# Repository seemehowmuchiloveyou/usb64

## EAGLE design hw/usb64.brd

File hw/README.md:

# Breakout PCB
* This board was designed using [Autodesk Eagle](https://www.autodesk.com/products/eagle/overview). You can edit the `.brd` and `.sch` with this program.
* You can order via KitSpace: https://kitspace.org/boards/github.com/ryzee119/usb64/.

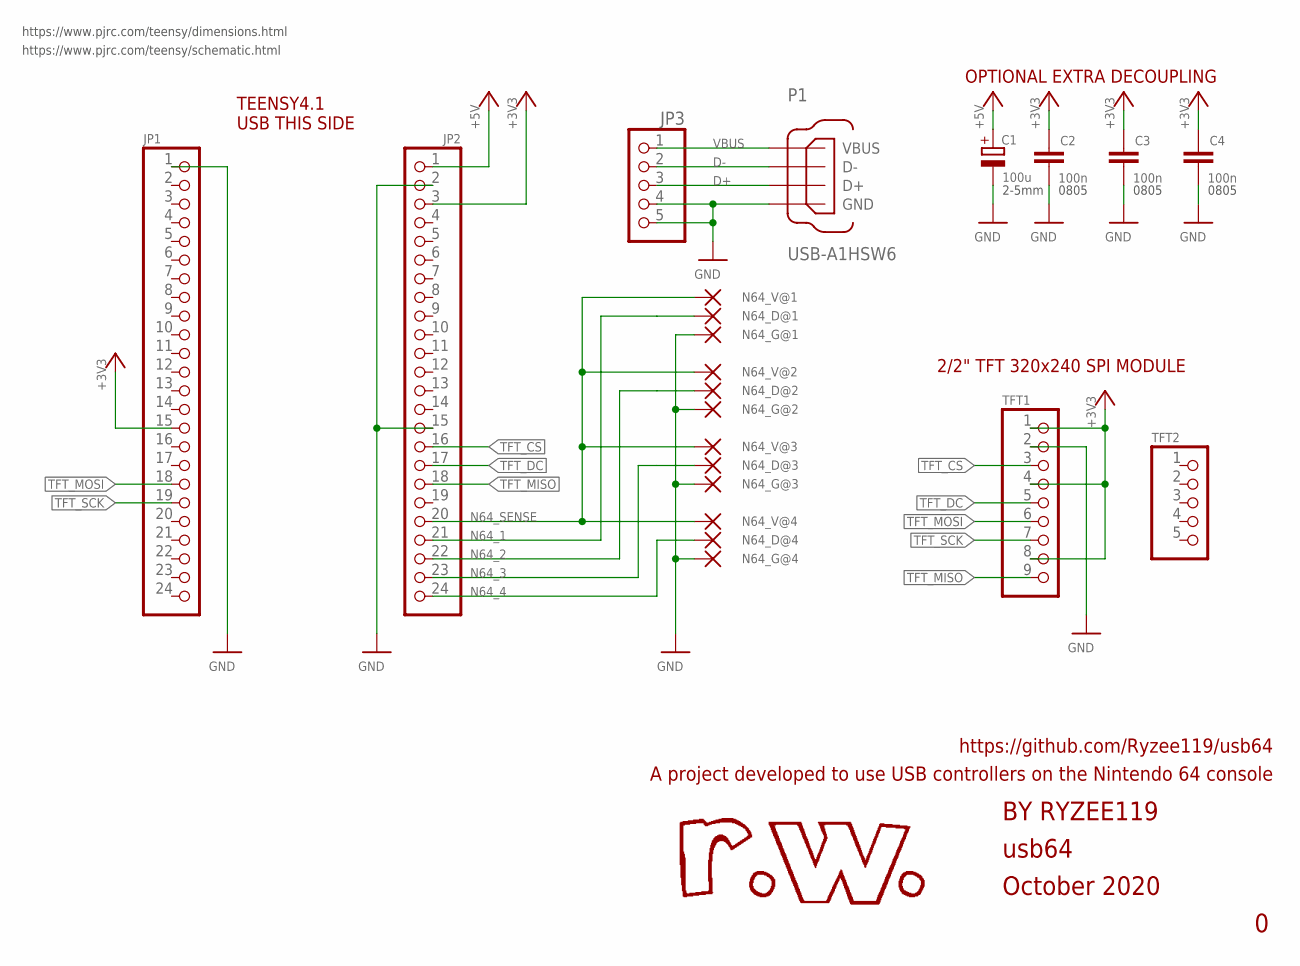
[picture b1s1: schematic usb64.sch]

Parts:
C1: 100u; E2-5
C2, C3, C4: 100n; C0805K
JP1, JP2: PINHD-1X24; 1X24
JP3: PINHD-1X5; 1X05
N64_D@1, N64_D@2, N64_D@3, N64_D@4, N64_G@1, N64_G@2, N64_G@3, N64_G@4, N64_V@1, N64_V@2, N64_V@3, N64_V@4: SMD2; SMD1,27-2,54
P1: USB-A1HSW6; OST_USB-A1HSW6
TFT1: PINHD-1X9; 1X09
TFT2: PINHD-1X5; 1X05

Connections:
+3V3: C2.1, C3.1, C4.1, JP1.15, JP2.3, TFT1.1, TFT1.4, TFT1.8
+5V: C1.+, JP2.1
D+: JP3.3, P1.3 (D+)
D-: JP3.2, P1.2 (D-)
GND: C1.-, C2.2, C3.2, C4.2, JP1.1, JP2.2, JP2.15, JP3.4, JP3.5, N64_G@1.1, N64_G@2.1, N64_G@3.1, N64_G@4.1, P1.4 (GND), TFT1.2
N64_1: JP2.21, N64_D@1.1
N64_2: JP2.22, N64_D@2.1
N64_3: JP2.23, N64_D@3.1
N64_4: JP2.24, N64_D@4.1
N64_SENSE: JP2.20, N64_V@1.1, N64_V@2.1, N64_V@3.1, N64_V@4.1
TFT_CS: JP2.16, TFT1.3
TFT_DC: JP2.17, TFT1.5
TFT_MISO: JP2.18, TFT1.9
TFT_MOSI: JP1.18, TFT1.6
TFT_SCK: JP1.19, TFT1.7
VBUS: JP3.1, P1.1 (VBUS)

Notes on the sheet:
usb64
October 2020
BY RYZEE119
A project developed to use USB controllers on the Nintendo 64 console
https://github.com/Ryzee119/usb64
TEENSY4.1 USB THIS SIDE
OPTIONAL EXTRA DECOUPLING
2/2" TFT 320x240 SPI MODULE
0805
2-5mm
https://www.pjrc.com/teensy/dimensions.html
https://www.pjrc.com/teensy/schematic.html

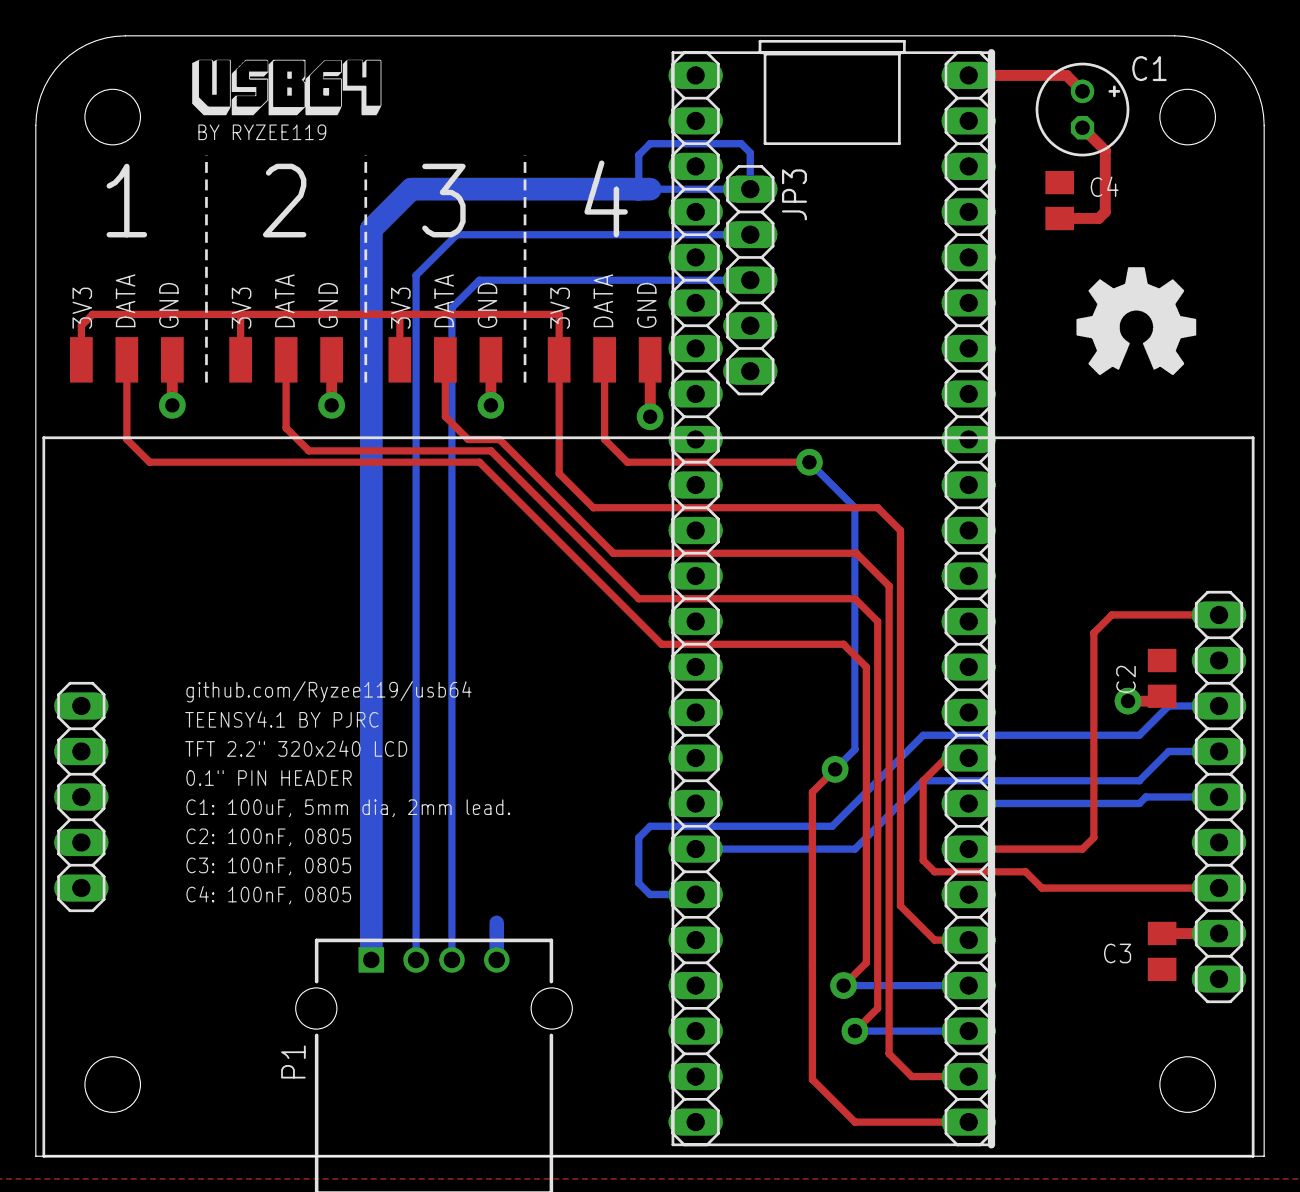
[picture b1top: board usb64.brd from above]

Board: 2 copper layers, 68.6 x 62.5 mm, 22 parts (0 on the bottom side), 16 nets.

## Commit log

2020-11-13 hw: Add breakout PCB
